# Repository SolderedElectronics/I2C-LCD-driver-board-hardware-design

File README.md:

# I2C LCD driver board Hardware design

## About the product

|  |
| :----------------------------------------------------------: |
|      [Buy I2C LCD driver board](https://www.solde.red/333003)      |

This adapter makes connection of LCD to Dasduino (or any other Arduino-compatible board) a breeze! It uses I2C communication which needs only two pins. It can be used and work with all of ours LCDs (16x2, 20x4, 16x4). Use our library and get started in few minutes of work!

It's even easier with easyC - no soldering is needed!

## Repository contents

All Soldered Electronics hardware designed in KiCAD, and repositories are organized in the following way:

- CAD folder - contains KiCAD files (Schematics, Board, Panel Board), sorted by version. Change log lists all changes between versions.
- OUTPUTS - contains useful files, such as Bill of Materials (BOM), PDF of schematics, 3D .step file of the board and gerber files, sorted by version. 
- OUTPUTS -> Compliance - Certificates and useful legal stuff. 

## Want to contribute?

Please feel free to submit a pull request if you have any contributions. We encourage you to submit an issue or pull request if you find a bug. 

## About Soldered

At Soldered, we design and manufacture a wide selection of electronic products to help you turn your ideas into acts and bring you one step closer to your final project. Our products are intented for makers and crafted in-house by our experienced team in Osijek, Croatia. We believe that sharing is a crucial element for improvement and innovation, and we work hard to stay connected with all our makers regardless of their skill or experience level. Therefore, all our products are open-source. Finally, we always have your back. If you face any problem concerning either your shopping experience or your electronics project, our team will help you deal with it, offering efficient customer service and cost-free technical support anytime. Some of those might be useful for you:

- [Web Store](https://www.soldered.com/shop)
- [Tutorials & Projects](https://soldered.com/learn)
- [Community & Technical support](https://soldered.com/community)

## License info

All Soldered open-source hardware (OSH) is under The TAPR Open Hardware License. Read more in the LICENSE file. 

No warranty - all designs in this repository are distributed in the hope that they will be useful, but without any warranty. They are provided "AS IS", therefore without warranty of any kind, either expressed or implied. The entire quality and performance of what you do with the contents of this repository are your responsibility. In no event, Soldered Electronics will be liable for your damages, losses, including any general, special, incidental or consequential damage arising out of the use or inability to use the contents of this repository. 

## Have fun! 
And thank you from your fellow makers at Soldered Electronics.

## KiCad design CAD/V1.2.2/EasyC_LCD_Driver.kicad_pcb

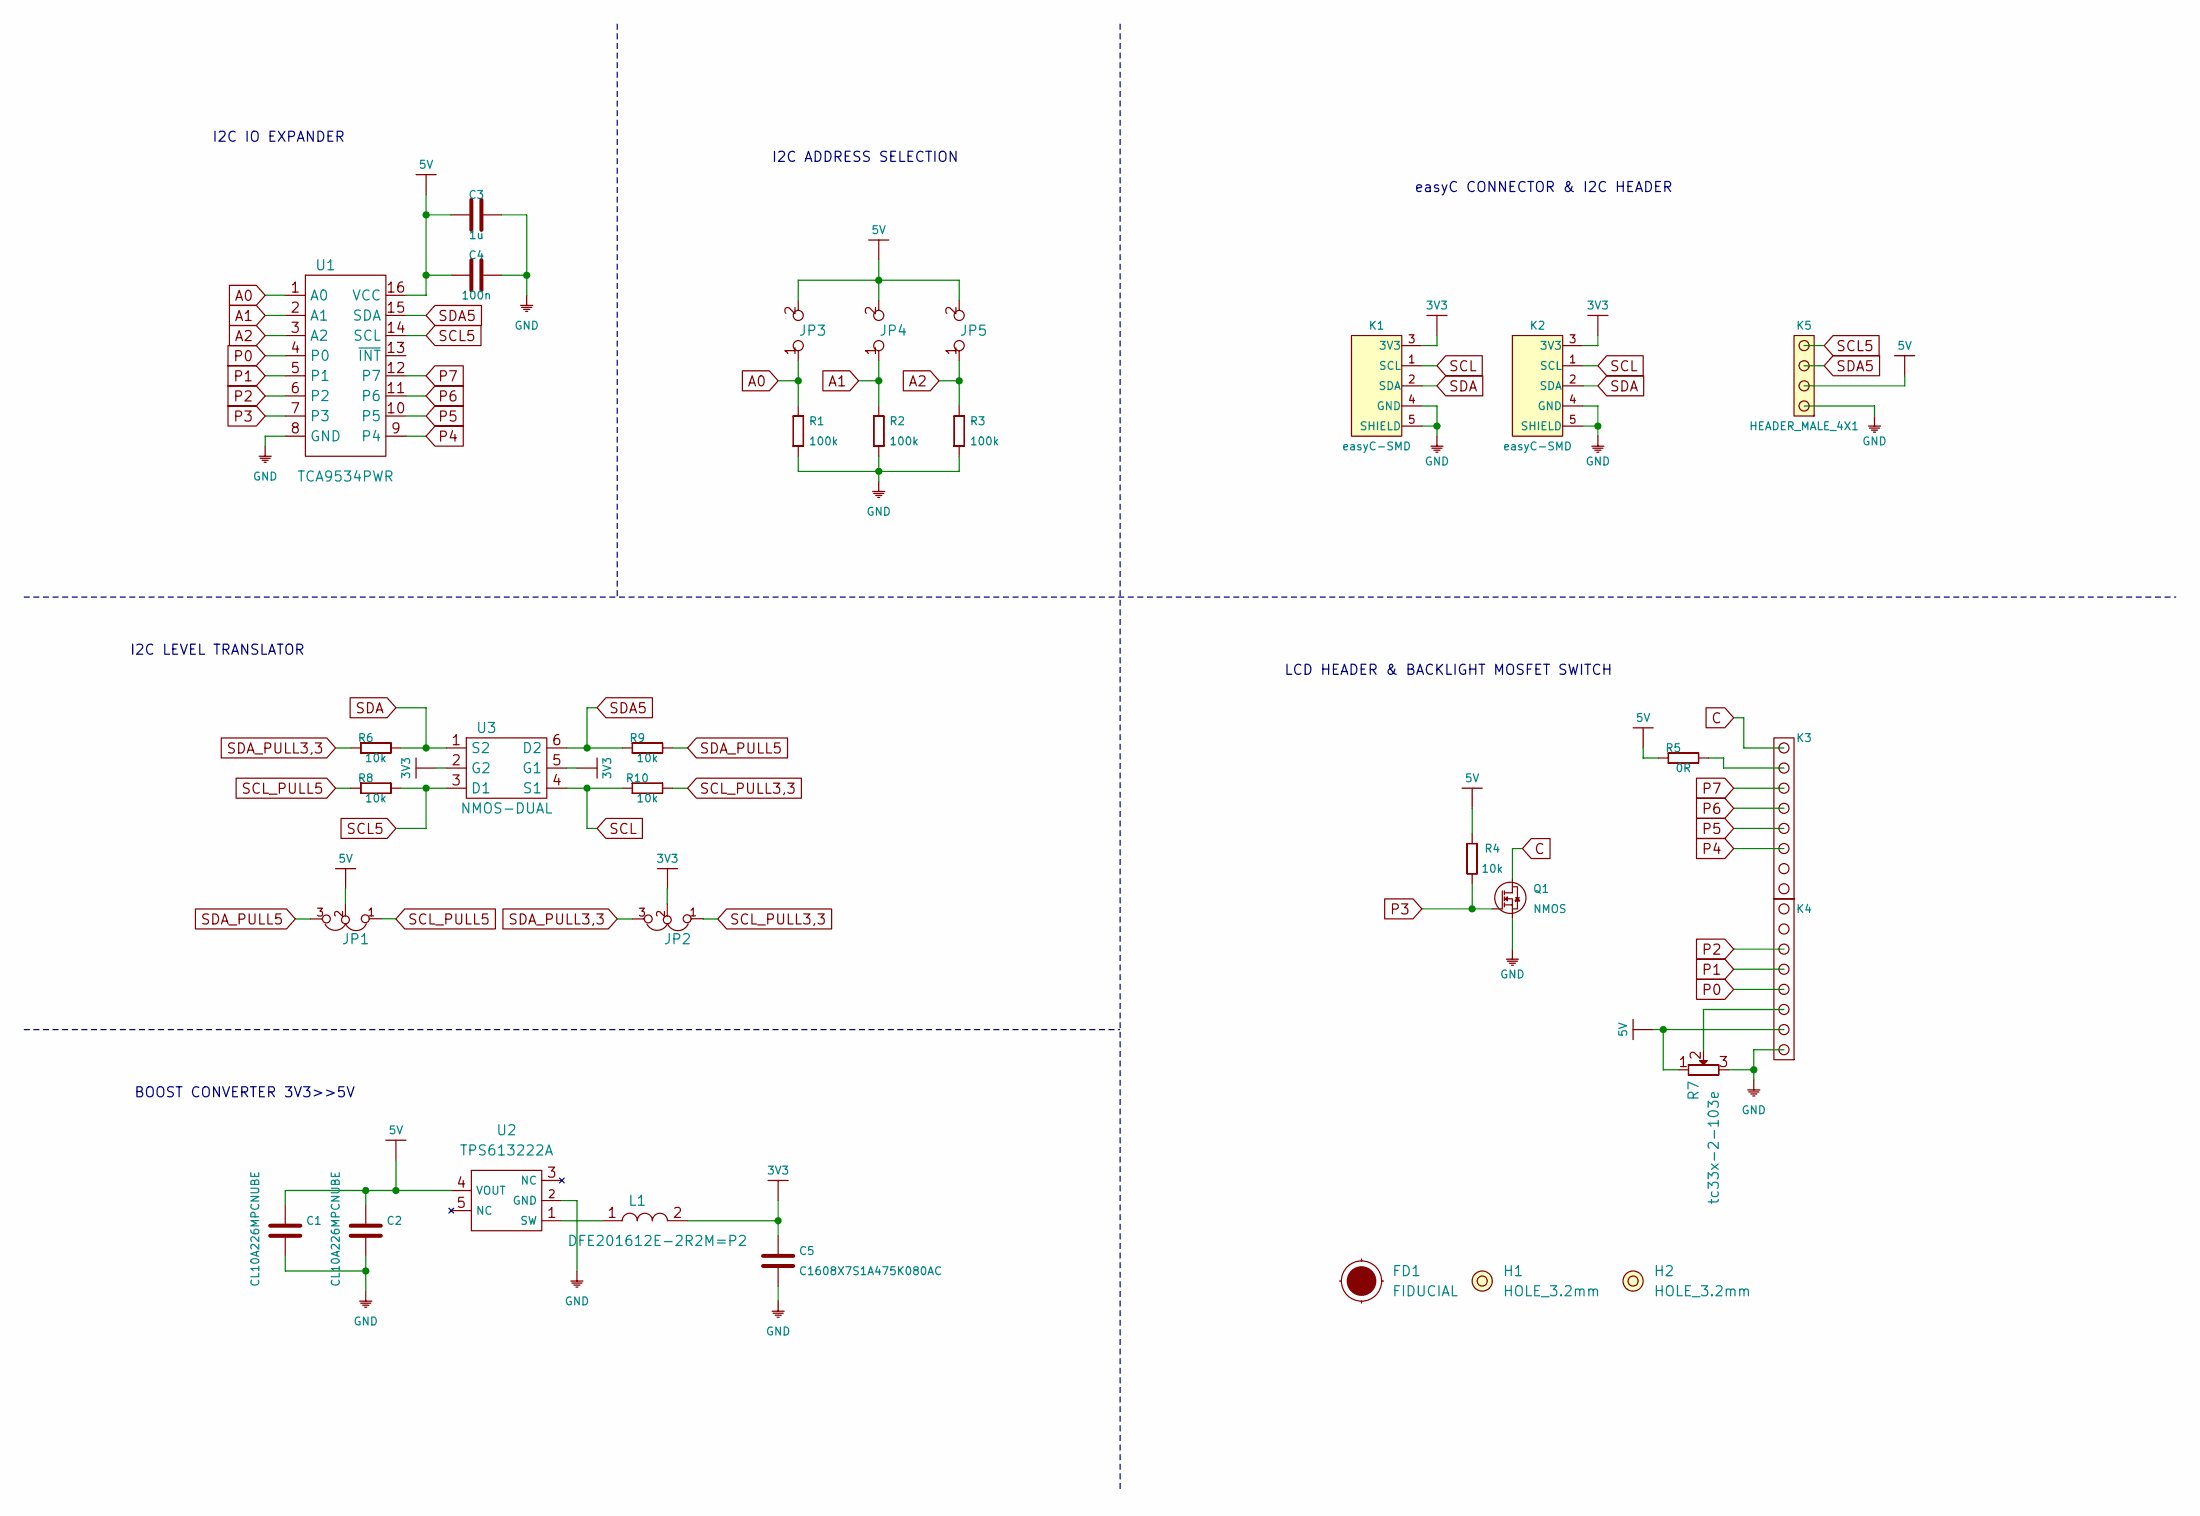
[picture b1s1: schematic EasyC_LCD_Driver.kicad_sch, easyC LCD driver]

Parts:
C1, C2: CL10A226MPCNUBE; 0805C
C3: 1u; 0603C
C4: 100n; 0603C
C5: C1608X7S1A475K080AC; 0805C
FD1: FIDUCIAL; FIDUCIAL_23
H1, H2: HOLE_3.2mm
JP1, JP2: SMD_JUMPER_3_PAD_TRACE
JP3, JP4, JP5: SMD_JUMPER
K1, K2: easyC-SMD; easyC-connector
K3, K4: HEADER_MALE_8X1
K5: HEADER_MALE_4X1
L1: DFE201612E-2R2M=P2; 0806L
Q1: NMOS; SOT-23-3
R1, R2, R3: 100k; 0603R
R4, R6, R8, R9, R10: 10k; 0603R
R5: 0R; 0603R
R7: tc33x-2-103e
U1: TCA9534PWR; TSSOP-16
U2: TPS613222A; tps613222a
U3: NMOS-DUAL; SOT-363

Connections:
3V3: C5.2, JP2.2, K1.3 (3V3), K2.3 (3V3), L1.2, U3.2 (G2), U3.5 (G1)
5V: C1.2, C2.2, C3.1, C4.1, JP1.2, JP3.2, JP4.2, JP5.2, K4.2, K5.2, R4.1, R5.1, R7.1, U1.16 (VCC), U2.4 (VOUT)
A0: JP3.1, R1.2, U1.1 (A0)
A1: JP4.1, R2.2, U1.2 (A1)
A2: JP5.1, R3.2, U1.3 (A2)
C: K3.8, Q1.3 (D)
GND: C1.1, C2.1, C3.2, C4.2, C5.1, K1.4 (GND), K1.5 (SHIELD), K2.4 (GND), K2.5 (SHIELD), K4.1, K5.1, Q1.2 (S), R1.1, R2.1, R3.1, R7.3, U1.8 (GND), U2.2 (GND)
unnamed: K3.7, R5.2
unnamed: K4.3, R7.2
unnamed: L1.1, U2.1 (SW)
P0: K4.4, U1.4 (P0)
P1: K4.5, U1.5 (P1)
P2: K4.6, U1.6 (P2)
P3: Q1.1 (G), R4.2, U1.7 (P3)
P4: K3.3, U1.9 (P4)
P5: K3.4, U1.10 (P5)
P6: K3.5, U1.11 (P6)
P7: K3.6, U1.12 (P7)
SCL: K1.1 (SCL), K2.1 (SCL), R10.1, U3.4 (S1)
SCL5: K5.4, R8.2, U1.14 (SCL), U3.3 (D1)
SCL_PULL3,3: JP2.1, R10.2
SCL_PULL5: JP1.1, R8.1
SDA: K1.2 (SDA), K2.2 (SDA), R6.2, U3.1 (S2)
SDA5: K5.3, R9.1, U1.15 (SDA), U3.6 (D2)
SDA_PULL3,3: JP2.3, R6.1
SDA_PULL5: JP1.3, R9.2

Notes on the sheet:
I2C ADDRESS SELECTION
I2C IO EXPANDER
LCD HEADER & BACKLIGHT MOSFET SWITCH
easyC CONNECTOR & I2C HEADER
I2C LEVEL TRANSLATOR
BOOST CONVERTER 3V3>>5V

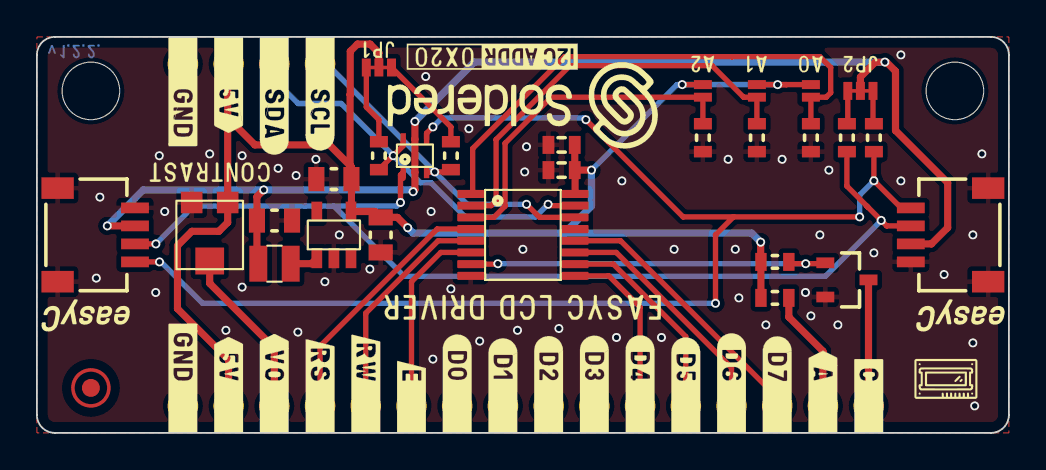
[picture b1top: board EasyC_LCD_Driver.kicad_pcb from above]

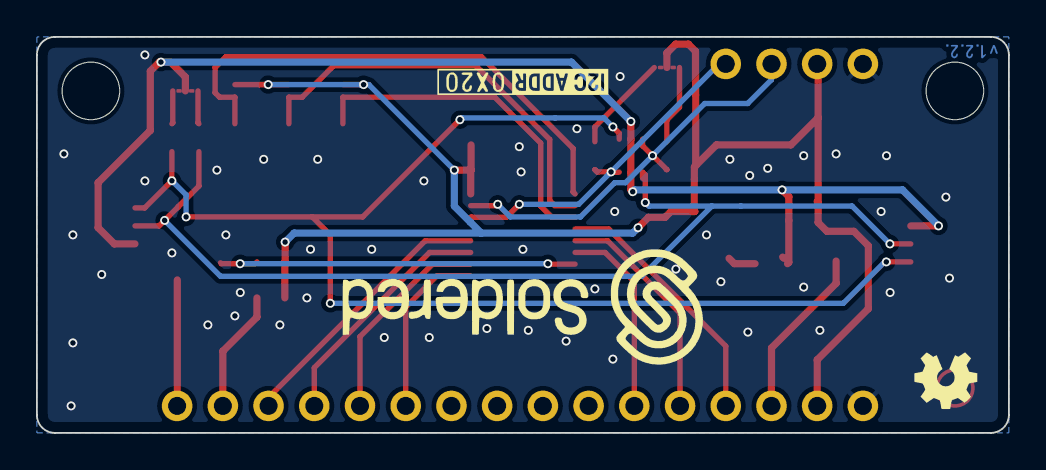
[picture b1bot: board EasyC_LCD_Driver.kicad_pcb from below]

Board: 2 copper layers, 54.0 x 22.0 mm, 33 parts (2 on the bottom side), 26 nets.

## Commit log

2022-08-06 Updating open source files.
